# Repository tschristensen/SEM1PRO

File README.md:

# SEM1PRO
Embedded Systems and Power Electronics - Semester Project
Thomas S. Christensen
Mikkel S. Jaedicke - mijae12@student.sdu.dk
Kyriakos Dovelos
Erlingur Ívar Jóhannsson
Martin Brøchner Andersen - marti11@student.sdu.dk

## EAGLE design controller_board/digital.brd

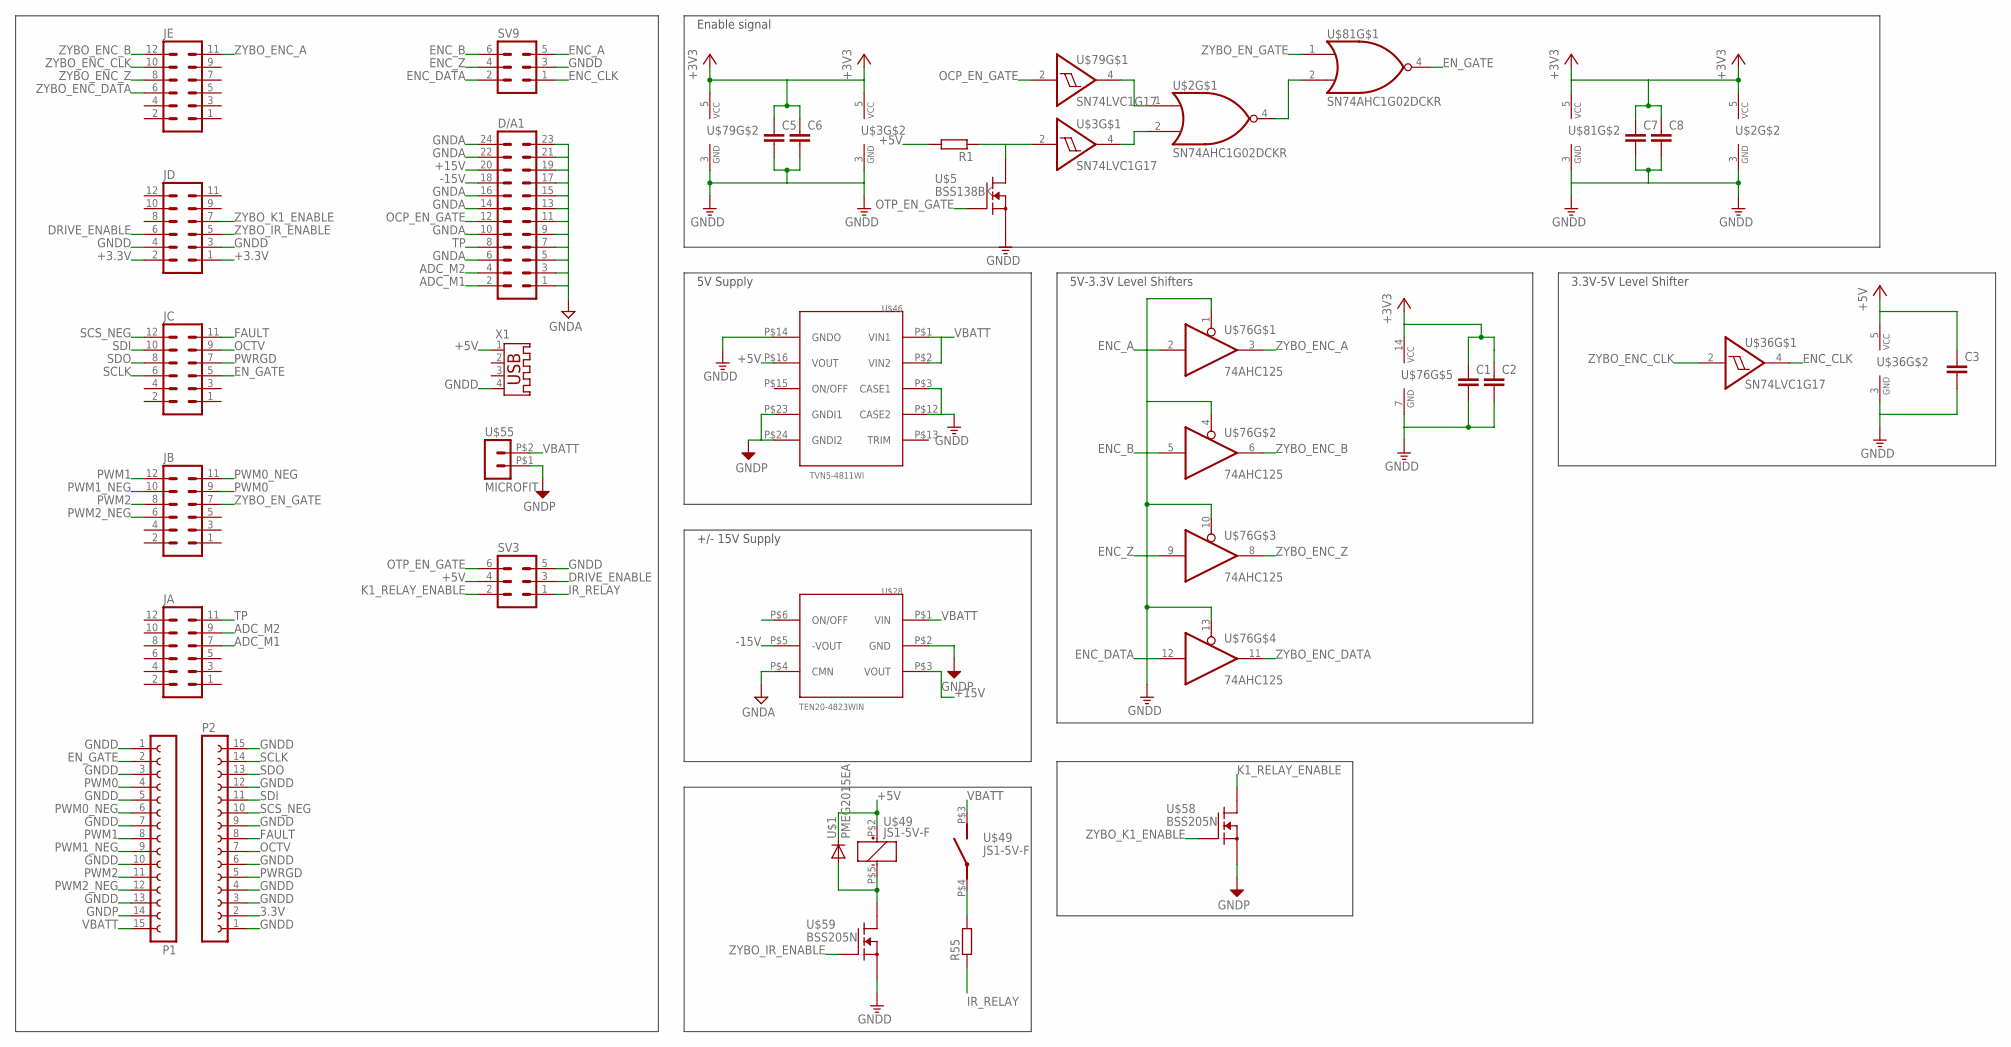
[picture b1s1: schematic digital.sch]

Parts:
C1, C2, C3, C5, C6, C7, C8: CC1206; C1206
D/A1: MA12-2
JA: MA06-2
JB: MA06-2
JC: MA06-2
JD: MA06-2
JE: MA06-2
P1, P2: FE15-1; FE15
R1, R55: RR1206; R1206
SV3, SV9: MA03-2
U$1: PMEG2015EA; SOD323_ST
U$2, U$81: SN74AHC1G02DCKR; SOT23-5
U$3, U$36, U$79: SN74LVC1G17; SOT23-5L
U$5: BSS138BK; SOT23
U$28: TEN20-4823WIN; TEN20-4823
U$46: TVN5-4811WI; DIP24
U$49: JS1-5V-F
U$55: MICROFIT; MICROFIT-3.0
U$58, U$59: BSS205N; SOT23
U$76: 74AHC125; SO14
X1: USB-A003

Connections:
3.3V: P2.2
+3.3V: JD.1, JD.2
+3V3: C1.1, C2.1, C5.1, C6.1, C7.1, C8.1, U$2.5 (VCC), U$3.5 (VCC), U$76.14 (VCC), U$79.5 (VCC), U$81.5 (VCC)
+5V: C3.1, R1.2, SV3.4, U$1.C, U$36.5 (VCC), U$46.P$16 (VOUT), U$49.P$2 (+), X1.1
+15V: D/A1.20, U$28.P$3 (VOUT)
-15V: D/A1.18, U$28.P$5 (-VOUT)
ADC_M1: D/A1.2, JA.7
ADC_M2: D/A1.4, JA.9
DRIVE_ENABLE: JD.6, SV3.3
ENC_A: SV9.5, U$76.2 (I)
ENC_B: SV9.6, U$76.5 (I)
ENC_CLK: SV9.1, U$36.4 (O)
ENC_DATA: SV9.2, U$76.12 (I)
ENC_Z: SV9.4, U$76.9 (I)
EN_GATE: JC.5, P1.2, U$81.4 (O)
FAULT: JC.11, P2.8
GNDA: D/A1.1, D/A1.3, D/A1.5, D/A1.6, D/A1.7, D/A1.9, D/A1.10, D/A1.11, D/A1.13, D/A1.14, D/A1.15, D/A1.16, D/A1.22, D/A1.23, D/A1.24, U$28.P$4 (CMN)
GNDD: C1.2, C2.2, C3.2, C5.2, C6.2, C7.2, C8.2, JD.3, JD.4, P1.1, P1.3, P1.5, P1.7, P1.10, P1.13, P2.1, P2.3, P2.4, P2.6, P2.9, P2.12, P2.15, SV3.5, SV9.3, U$2.3 (GND), U$3.3 (GND), U$5.2 (S), U$36.3 (GND), U$46.P$3 (CASE1), U$46.P$12 (CASE2), U$46.P$14 (GNDO), U$59.2 (S), U$76.1 (OE), U$76.4 (OE), U$76.7 (GND), U$76.10 (OE), U$76.13 (OE), U$79.3 (GND), U$81.3 (GND), X1.4
GNDP: P1.14, U$28.P$2 (GND), U$46.P$23 (GNDI1), U$46.P$24 (GNDI2), U$55.P$1 (2), U$58.2 (S)
IR_RELAY: R55.1, SV3.1
K1_RELAY_ENABLE: SV3.2, U$58.3 (D)
unnamed: R1.1, U$3.2 (I), U$5.3 (D)
unnamed: U$2.4 (O), U$81.2 (I1)
unnamed: R55.2, U$49.P$4
unnamed: U$1.A, U$49.P$5 (-), U$59.3 (D)
OCP_EN_GATE: D/A1.12, U$79.2 (I)
OCTV: JC.9, P2.7
OTP_EN_GATE: SV3.6, U$5.1 (G)
PWM0: JB.9, P1.4
PWM0_NEG: JB.11, P1.6
PWM1: JB.12, P1.8
PWM1_NEG: JB.10, P1.9
PWM2: JB.8, P1.11
PWM2_NEG: JB.6, P1.12
PWRGD: JC.7, P2.5
SCLK: JC.6, P2.14
SCS_NEG: JC.12, P2.10
SDI: JC.10, P2.11
SDO: JC.8, P2.13
TP: D/A1.8, JA.11
VBATT: P1.15, U$28.P$1 (VIN), U$46.P$1 (VIN1), U$46.P$2 (VIN2), U$49.P$3 (S), U$55.P$2 (3)
ZYBO_ENC_A: JE.11, U$76.3 (O)
ZYBO_ENC_B: JE.12, U$76.6 (O)
ZYBO_ENC_CLK: JE.10, U$36.2 (I)
ZYBO_ENC_DATA: JE.6, U$76.11 (O)
ZYBO_ENC_Z: JE.8, U$76.8 (O)
ZYBO_EN_GATE: JB.7, U$81.1 (I0)
ZYBO_IR_ENABLE: JD.5, U$59.1 (G)
ZYBO_K1_ENABLE: JD.7, U$58.1 (G)
ZYBO_OCP_EN_GATE: JB.5, U$2.1 (I0), U$79.4 (O)
ZYBO_OTP_EN_GATE: JD.8, U$2.2 (I1), U$3.4 (O)

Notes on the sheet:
Enable signal
5V-3.3V Level Shifters
3.3V-5V Level Shifter
+/- 15V Supply
5V Supply

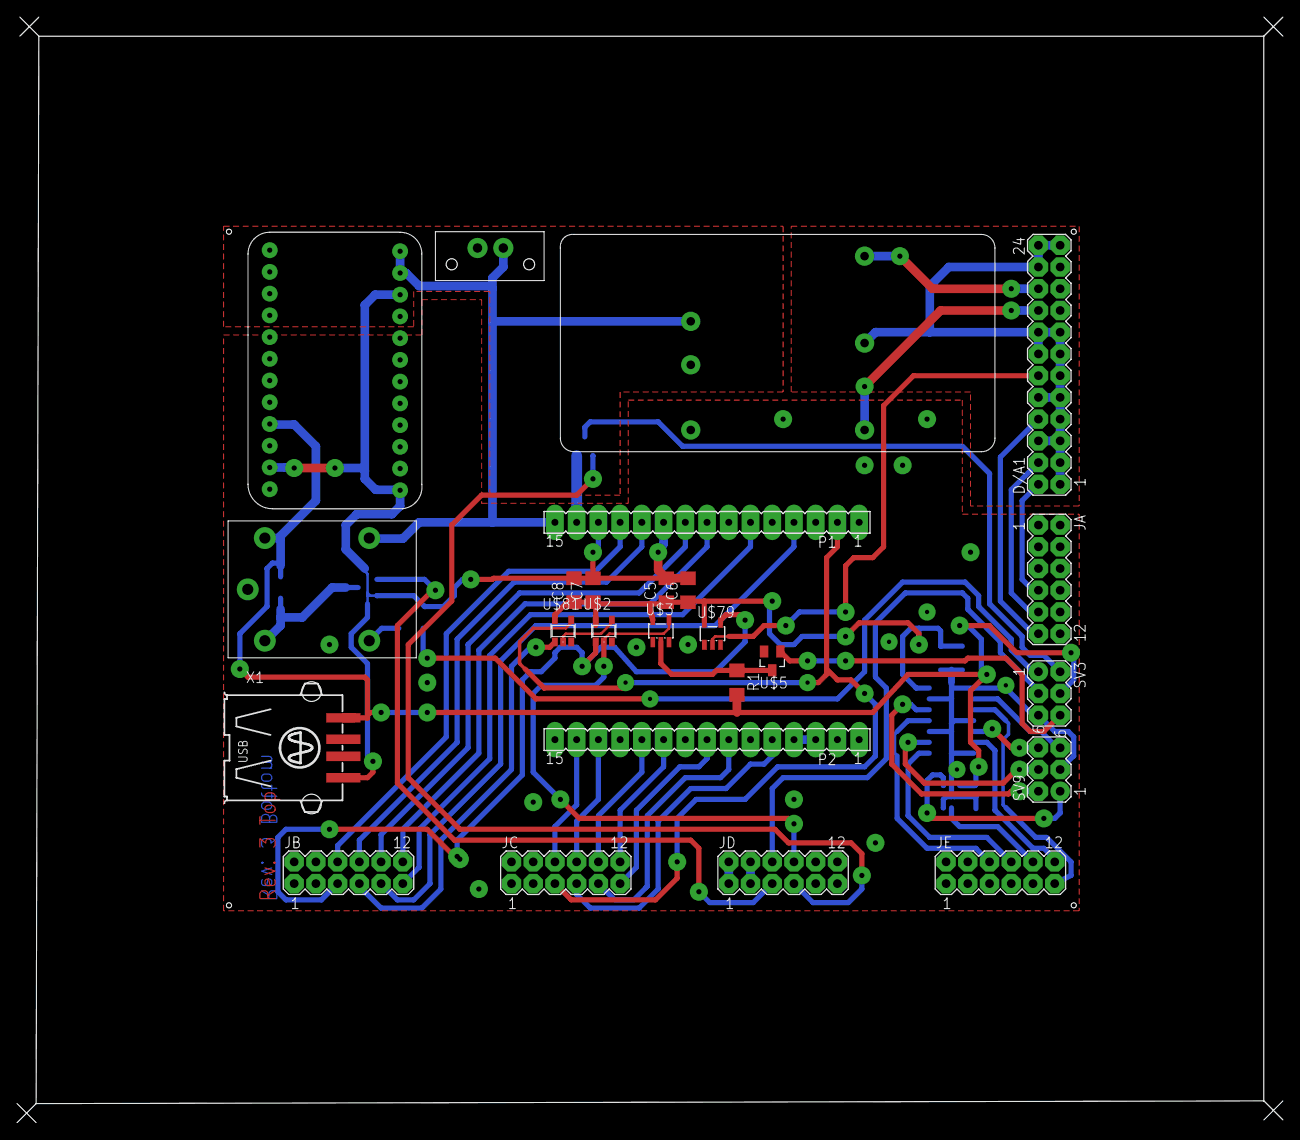
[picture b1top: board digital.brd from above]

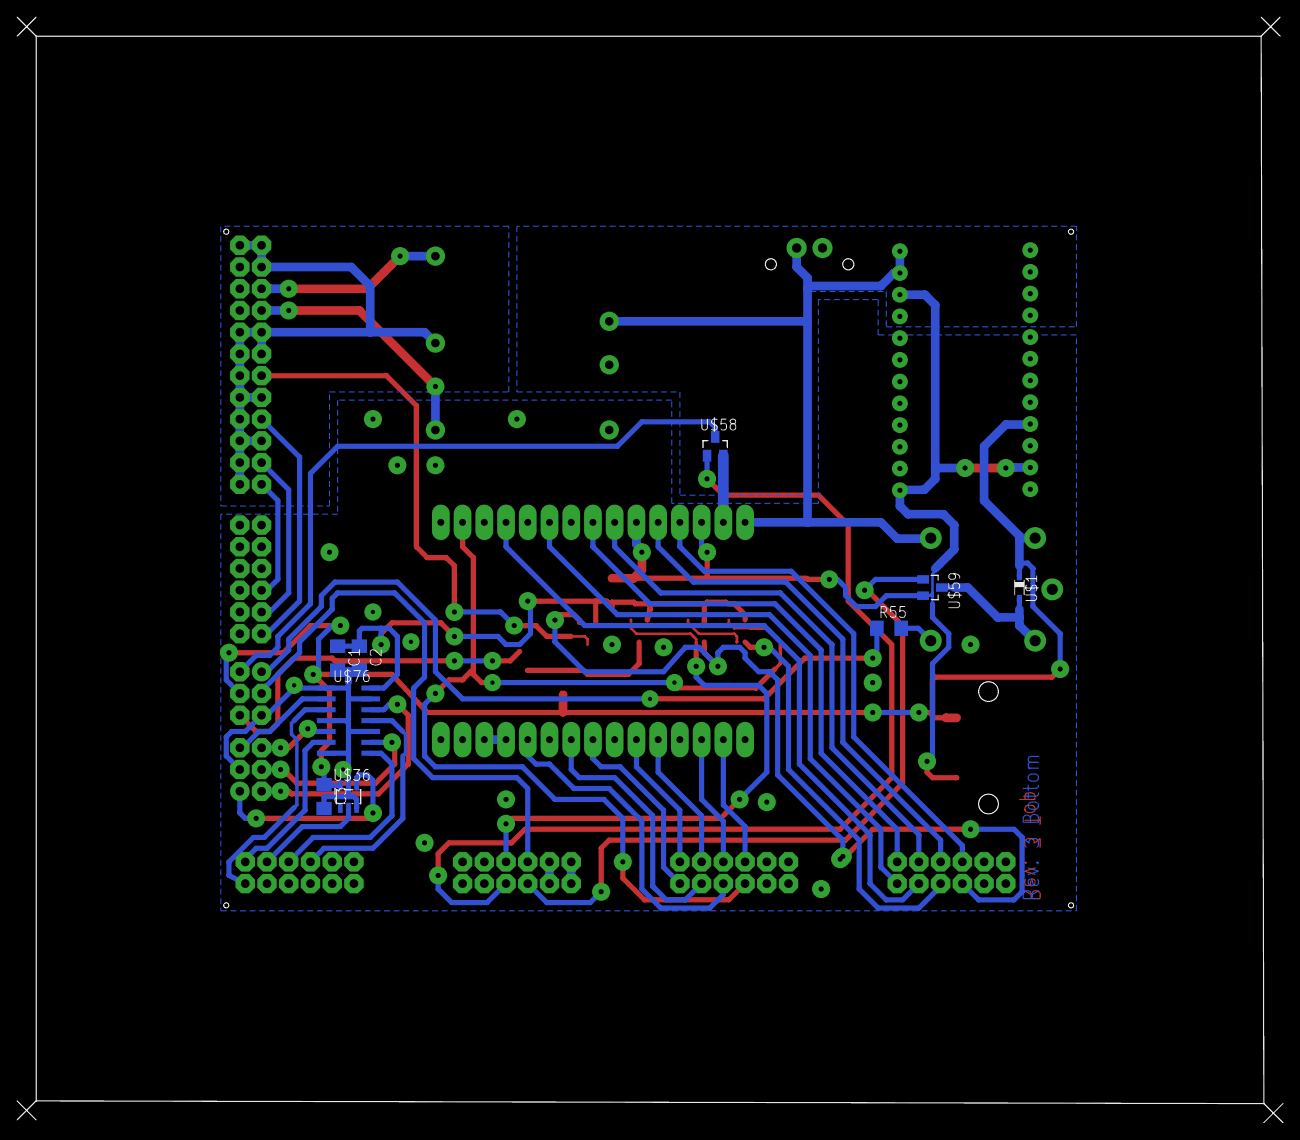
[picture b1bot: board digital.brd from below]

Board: 2 copper layers, 148.0 x 129.2 mm, 34 parts (9 on the bottom side), 50 nets.

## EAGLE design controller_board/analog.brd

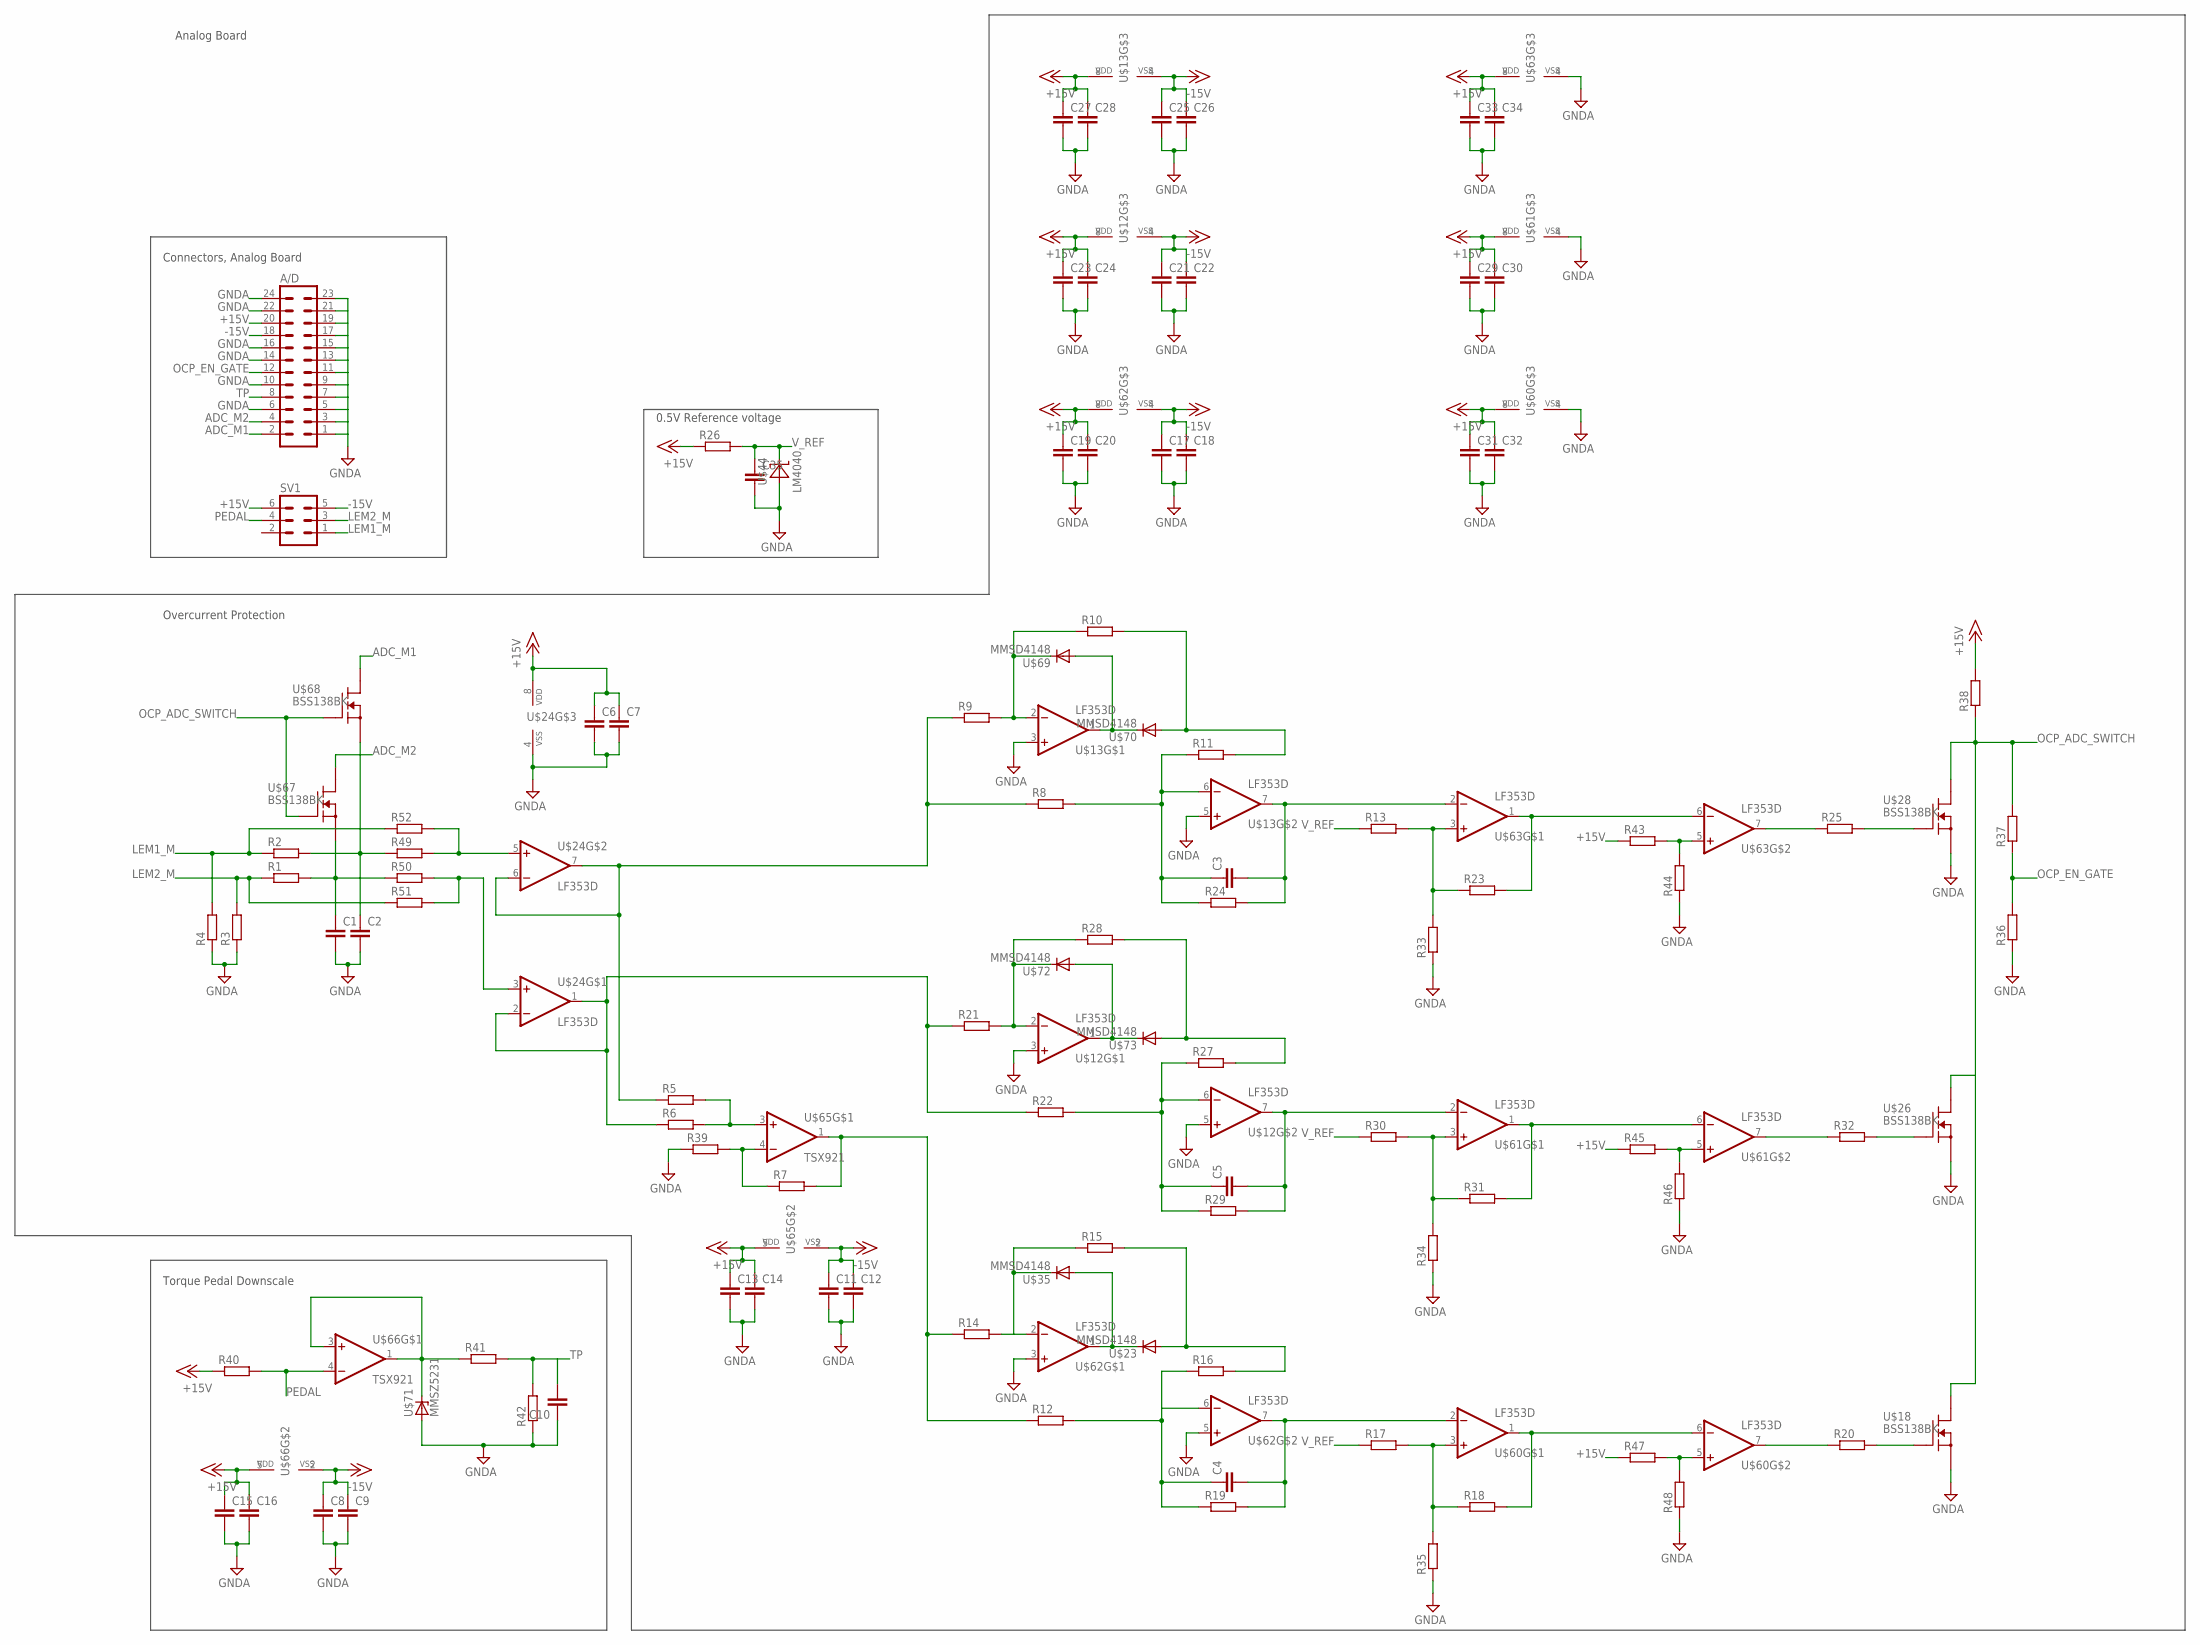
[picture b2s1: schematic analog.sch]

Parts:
A/D: MA12-2
C1, C2, C6, C7, C8, C9, C11, C12, C13, C14, C15, C16, C17, C18, C19, C20, C21, C22, C23, C24, C25, C26, C27, C28, C29, C30, C31, C32, C33, C34, C35: CC1206; C1206
C3, C4, C5, C10: C-EUC0805; C0805
R1, R2, R3, R4, R5, R6, R7, R8, R9, R10, R11, R12, R13, R14, R15, R16, R17, R18, R19, R20, R21, R22, R23, R24, R25, R26, R27, R28, R29, R30, R31, R32, R33, R34, R35, R36, R37, R38, R39, R40, R41, R42, R43, R44, R45, R46, R47, R48, R49, R50, R51, R52: R-EU_M0805; M0805
SV1: MA03-2
U$12, U$13, U$24, U$60, U$61, U$62, U$63: LF353D; SO08
U$18, U$26, U$28, U$67, U$68: BSS138BK; SOT23
U$23, U$35, U$69, U$70, U$72, U$73: MMSD4148; SOD123
U$44: LM4040; SOT23
U$65, U$66: TSX921; SOT23-5
U$71: MMSZ5231; SOD123

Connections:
+15V: A/D.20, C6.1, C7.1, C13.1, C14.1, C15.1, C16.1, C19.1, C20.1, C23.1, C24.1, C27.1, C28.1, C29.1, C30.1, C31.1, C32.1, C33.1, C34.1, R26.1, R38.2, R40.1, R43.1, R45.1, R47.1, SV1.6, U$12.8 (VDD), U$13.8 (VDD), U$24.8 (VDD), U$60.8 (VDD), U$61.8 (VDD), U$62.8 (VDD), U$63.8 (VDD), U$65.5 (VDD), U$66.5 (VDD)
-15V: A/D.18, C8.1, C9.1, C11.1, C12.1, C17.1, C18.1, C21.1, C22.1, C25.1, C26.1, SV1.5, U$12.4 (VSS), U$13.4 (VSS), U$62.4 (VSS), U$65.2 (VSS), U$66.2 (VSS)
ADC_M1: A/D.2, U$68.3 (D)
ADC_M2: A/D.4, U$67.3 (D)
GNDA: A/D.1, A/D.3, A/D.5, A/D.6, A/D.7, A/D.9, A/D.10, A/D.11, A/D.13, A/D.14, A/D.15, A/D.16, A/D.22, A/D.23, A/D.24, C1.2, C2.2, C6.2, C7.2, C8.2, C9.2, C10.1, C11.2, C12.2, C13.2, C14.2, C15.2, C16.2, C17.2, C18.2, C19.2, C20.2, C21.2, C22.2, C23.2, C24.2, C25.2, C26.2, C27.2, C28.2, C29.2, C30.2, C31.2, C32.2, C33.2, C34.2, C35.2, R3.1, R4.1, R33.1, R34.1, R35.1, R36.1, R39.1, R42.1, R44.1, R46.1, R48.1, U$12.3 (+IN), U$12.5 (+IN), U$13.3 (+IN), U$13.5 (+IN), U$18.2 (S), U$24.4 (VSS), U$26.2 (S), U$28.2 (S), U$44.1 (A), U$60.4 (VSS), U$61.4 (VSS), U$62.3 (+IN), U$62.5 (+IN), U$63.4 (VSS), U$71.A
LEM1_M: R2.1, R4.2, R52.1, SV1.1
LEM2_M: R1.1, R3.2, R51.1, SV1.3
unnamed: R50.2, R51.2, U$24.3 (+IN)
unnamed: R5.1, R8.1, R9.1, U$24.6 (-IN), U$24.7 (OUT)
unnamed: R9.2, R10.1, U$13.2 (-IN), U$69.C
unnamed: C2.1, R2.2, R49.1, U$68.2 (S)
unnamed: R13.2, R23.1, R33.2, U$63.3 (+IN)
unnamed: R5.2, R6.2, U$65.3 (+IN)
unnamed: R7.2, R12.1, R14.1, U$65.1 (OUT)
unnamed: C3.1, R8.2, R11.1, R24.1, U$13.6 (-IN)
unnamed: R10.2, R11.2, U$70.A
unnamed: C3.2, R24.2, U$13.7 (OUT), U$63.2 (-IN)
unnamed: U$13.1 (OUT), U$69.A, U$70.C
unnamed: R6.1, R21.1, R22.1, U$24.1 (OUT), U$24.2 (-IN)
unnamed: R14.2, R15.1, U$35.C, U$62.2 (-IN)
unnamed: C4.1, R12.2, R16.1, R19.1, U$62.6 (-IN)
unnamed: U$23.C, U$35.A, U$62.1 (OUT)
unnamed: R15.2, R16.2, U$23.A
unnamed: C4.2, R19.2, U$60.2 (-IN), U$62.7 (OUT)
unnamed: R23.2, U$63.1 (OUT), U$63.6 (-IN)
unnamed: R17.2, R18.1, R35.2, U$60.3 (+IN)
unnamed: R18.2, U$60.1 (OUT), U$60.6 (-IN)
unnamed: R32.1, U$61.7 (OUT)
unnamed: R7.1, R39.2, U$65.4 (-IN)
unnamed: R21.2, R28.1, U$12.2 (-IN), U$72.C
unnamed: C5.1, R22.2, R27.1, R29.1, U$12.6 (-IN)
unnamed: U$12.1 (OUT), U$72.A, U$73.C
unnamed: R27.2, R28.2, U$73.A
unnamed: C5.2, R29.2, U$12.7 (OUT), U$61.2 (-IN)
unnamed: R30.2, R31.1, R34.2, U$61.3 (+IN)
unnamed: R31.2, U$61.1 (OUT), U$61.6 (-IN)
unnamed: R45.2, R46.2, U$61.5 (+IN)
unnamed: R25.1, U$63.7 (OUT)
unnamed: R25.2, U$28.1 (G)
unnamed: R32.2, U$26.1 (G)
unnamed: R20.2, U$18.1 (G)
unnamed: R41.1, U$66.1 (OUT), U$66.3 (+IN), U$71.C
unnamed: R43.2, R44.2, U$63.5 (+IN)
unnamed: R47.2, R48.2, U$60.5 (+IN)
unnamed: R20.1, U$60.7 (OUT)
unnamed: R49.2, R52.2, U$24.5 (+IN)
unnamed: C1.1, R1.2, R50.1, U$67.2 (S)
OCP_ADC_SWITCH: R37.2, R38.1, U$18.3 (D), U$26.3 (D), U$28.3 (D), U$67.1 (G), U$68.1 (G)
OCP_EN_GATE: A/D.12, R36.2, R37.1
PEDAL: R40.2, SV1.4, U$66.4 (-IN)
TP: A/D.8, C10.2, R41.2, R42.2
V_REF: C35.1, R13.1, R17.1, R26.2, R30.1, U$44.2 (C)

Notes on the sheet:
Torque Pedal Downscale
Overcurrent Protection
0.5V Reference voltage
Analog Board
Connectors, Analog Board

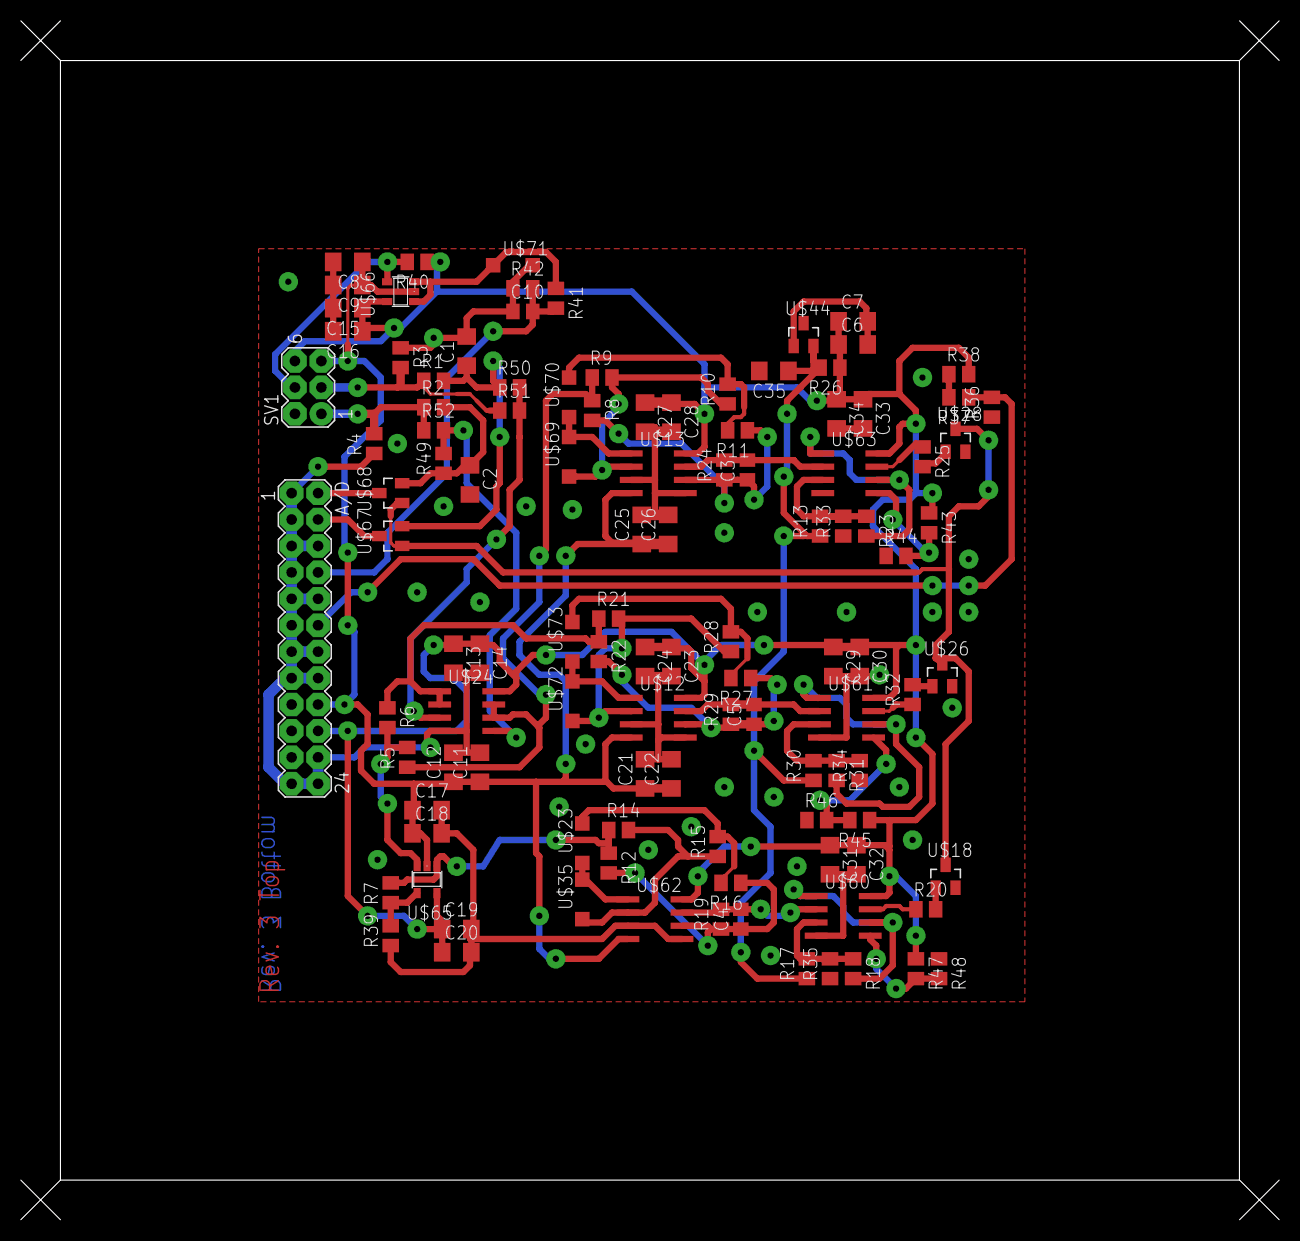
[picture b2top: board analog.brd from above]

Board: 2 copper layers, 121.0 x 115.3 mm, 111 parts (0 on the bottom side), 52 nets.

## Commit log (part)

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2016-03-09 edit my name
2016-03-09 Message
2016-03-09 Added my name and email
2016-03-09 Conflict Resolved!
2016-03-09 lkljlkj
2016-03-09 added a name
2016-03-09 Test
2016-03-09 useless
2016-03-15 Added initial report structure and .gitignore
2016-03-16 Added my date of birth
2016-03-16 added a name to the readme.md file
2016-03-16 Added my name, and wrote the RIGHT email.
2016-03-16 Uploaded my four suggestions for power transistors
2016-03-17 Added name to titlepage and configuration line for my system
2016-03-17 inserted birthday
2016-04-01 added schematics
2016-04-01 added schematic pdf
2016-04-07 added Note for logic level converters
2016-04-10 added some pics
2016-04-10 Added datasheets for controller and buckconverter + initial draft of logic level converters and Torque pedal scaledown
2016-04-10 more datasheets
2016-04-13 Added figures for controller board section
2016-04-14 set up the report to include all the sections i think are needed.
2016-04-14 Added board schematic
2016-04-14 added pic
2016-04-14 updated board scematic
2016-04-14 Yet another schematic update!
2016-04-20 added TI application note and updates to report
2016-04-20 report changed a little. some sections added
2016-04-21 agenda
2016-04-21 meeting agenda updated.
2016-04-22 Started writing on PMACmotor
2016-04-22 Added simulation folder with lots of nice stuff to be confused about
2016-04-22 updated simulations, added KE measurements
2016-04-22 added full system diagram V1.0
2016-04-22 just some more words
2016-04-24 wrote some more on PMAC
2016-04-25 added battery to resources and started writing system discription
2016-04-25 edited bib.tex, and added datasheets (I think)
2016-04-26 added plecs model with PWM switch mode and heatsinks
2016-04-27 Added small motor project
2016-04-27 blank
2016-04-28 updatet power loss simulations
2016-04-30 Added BOM for analog board
2016-05-02 so this cannot be empty?
2016-05-03 Got tortoiseGit (for windows) working. And uploaded datasheet for our mosfets.
2016-05-04 Plecs models with and without SVN
2016-05-04 blockdiagram
2016-05-04 added blockdiagram
2016-05-04 no changes made. i just checked the diagram
2016-05-04 added small_motor3 project
2016-05-04 Added board schematics and board layouts, open with eagle
2016-05-04 fixed introduction
2016-05-04 Started writing on Simulations
2016-05-05 fixed an error
2016-05-05 Uploaded possibly faulty simulation
2016-05-05 controller changes
2016-05-05 Uploaded document about scmitt triggers
2016-05-05 Pull commit
2016-05-05 A days work on simulation.tex, and general simulations.
2016-05-05 Discretesized controller-
2016-05-06 Fixed diagram
2016-05-06 Updated simulations. Now I'll head home, and have my desktop work on them for a day or two.
2016-05-06 writing system overview
2016-05-06 writing more to system descrption.
2016-05-06 okok
2016-05-07 changed pictures. they were too big, took ages to build.
2016-05-07 more writing. system stuff
2016-05-07 Did some simulations
2016-05-08 In simulations: Quantized encoder feedback, switched to lookup tables (realistic, not sure it's any faster in simulations). Wrote more about Simulations.
2016-05-09 changed filenames. PNG -> png
2016-05-09 Uploaded rough version of board documentation
2016-05-09 Added graphics for boardlayout
2016-05-09 skod program
2016-05-09 Added meeting details from today
2016-05-09 meeting details
2016-05-09 Pedal
2016-05-09 diagrams
2016-05-09 Added PMSM state space model and paper about state space.
2016-05-09 Half days work
2016-05-10 PDF DIAGRAMS
2016-05-10 fixed something
2016-05-10 Revision of Diagrams
2016-05-10 pdf also
2016-05-10 added some mosfet stuff
2016-05-10 made small adjustmens of text and added lots of todos
2016-05-10 Model changes state space. made transfer function.
2016-05-11 added figures of motor model
2016-05-11 Added section of logic level shifters and drive enable signals!
2016-05-11 control ki kp added
2016-05-11 worked on the model.
2016-05-12 found kp and ki from transfer function + settling time formula.
2016-05-12 wrote comments to the control parameters
2016-05-12 updates to boards
2016-05-12 added some text and stuff
2016-05-12 Added a new section for the state space model and finding parameters of kp and ki. added 5 graphics and changed main file.
2016-05-12 fixed motor model figs
2016-05-12 added driver enable signal bit
2016-05-13 writing continues
2016-05-13 uploading graphics fix
2016-05-13 added some text n' stuff
2016-05-13 wrote about transfer function and deriving control values
2016-05-13 introduction.tex AND REF
2016-05-13 did nothing
2016-05-13 added graphic
2016-05-13 added missing figures
2016-05-13 fixed some errors
2016-05-14 Managed to add a crude brake and tire slip. Pretty proud of it, just have to fine tune it.
2016-05-14 Tweaked the brake
2016-05-16 added more report
2016-05-16 removed controller board section, this is replaced by boardlayout
2016-05-16 New report structure and tons of todos
2016-05-16 added extended layout section
2016-05-16 added a tiny bit
2016-05-16 no changes
2016-05-16 added a lot to system description
2016-05-16 added a bit
2016-05-16 added many more todos and the siunitx package
2016-05-16 fixed main
2016-05-16 changs to system diagram
2016-05-16 added graphics
2016-05-16 More todos,
2016-05-17 added section about small test
2016-05-17 added graph
2016-05-17 Read through PMAC
2016-05-17 added an ADC section
2016-05-17 Done reading and todoing this revision, except controller part
2016-05-17 added small section about encoders
2016-05-17 Responded to the comments, Thomas made to some of my text.
2016-05-17 Remade some diagrams for the zybo section with tikz, wrote a lot more to state space model section and added some pictures. Still need a lot of work on model section.
2016-05-17 changed the figures to tikz in zybo section
2016-05-17 Plecs
2016-05-19 Added/changed system analysis slightly
2016-05-20 writings from yesterday.
2016-05-21 Some model/control changes. + writing
2016-05-21 added Xilinx project
2016-05-21 Who knows!
2016-05-21 removed big file
2016-05-21 fixed mistake
2016-05-21 lots of changes to model stuff.
2016-05-22 Added some sunday graphs
2016-05-23 new task diagram updated
2016-05-23 nothing special
2016-05-23 corrections
2016-05-23 cccc
2016-05-23 added stuff about mosfets, not finished
2016-05-23 new pictures. more text. more correctness
2016-05-24 aaaa
2016-05-24 trying to correct and extend intro
2016-05-24 added some figs and more
2016-05-24 changes to stuff nd junk! mostly controller stuff
2016-05-25 Changes to Electronics Design
2016-05-25 added missing picture...
2016-05-25 task diagram changes
2016-05-25 small changes
2016-05-25 added Kyriakos's thing
2016-05-25 finished control
2016-05-25 More SPI and change to main.tex to make figure texts smaller
2016-05-25 more spi...
2016-05-25 sada
2016-05-25 Little bit of writing, little bit of simulations. Lots of analog board work, but that's not evident here.
2016-05-26 fixing an error
2016-05-26 added ocp data
2016-05-26 Wrote a lot about pole zero
2016-05-26 Added some text!
2016-05-26 George managed to get me thinking so I couldn't fall asleep. Turns out I'm still right
2016-05-27 Writing stuff
2016-05-27 removed Kyriakos text and added some definements for my code
2016-05-27 ocp underscore data
2016-05-27 done deal
2016-05-27 added text about controller
2016-05-27 little bit reading through motormodel.tex
2016-05-27 Writing on Simulations
2016-05-28 fixed data
2016-05-28 fixed some shit
2016-05-28 Fixed bib.tex
2016-05-28 Baaaaaaaaaaaaaaaaaah, annoying
2016-05-28 I don't remember what I did
2016-05-28 added missing graphics
2016-05-28 pulpupllpullpul
2016-05-28 added missing grpahics
2016-05-28 lalallalala
2016-05-28 added tikz
2016-05-28 added graph and text
2016-05-28 workworkworkworkwork
2016-05-28 Added half inverter section
2016-05-28 added task digram
2016-05-28 added single phase diagram
2016-05-28 adding to mosfet section
2016-05-28 more tikz
2016-05-28 added some and tried to change titlepage. Not finished. We should tallk.
2016-05-28 Fucking real madrid won. Now I'm sad!
2016-05-28 Still sad!
2016-05-28 my zection is readzy!
2016-05-28 added more stuff to mosfets and some figs
2016-05-29 changed all figures in my section. Trim is fucking me over though. will fix tomorrow
2016-05-29 sooo tired
2016-05-29 Added a main.tex file without all the sections ignored.
2016-05-29 readtrough of electronic part
2016-05-29 Todos in Mikkels section
2016-05-29 Looked through threephaseinverter.tex, and commented on what I saw. It's still too short for my taste.
2016-05-29 something git wanted
2016-05-29 A beautiful Branch!
2016-05-29 Cropped all the pictures using NITRO! great program ! :D
2016-05-29 changed some in system anal
2016-05-29 Hello World
2016-05-29 just some un commenting
2016-05-29 redone corrections
2016-05-29 fixed some erlingur notes. not done at all. reading martins now
2016-05-29 added text about time freq
2016-05-29 Added graphics and corrections to electronics
2016-05-29 little bit confusing
2016-05-29 red through simulation added comments
2016-05-29 Beginning sections read again
2016-05-29 added nice graphs
2016-05-29 added the actual graphs
2016-05-29 some todo changes
2016-05-29 Wrote something aobut caps... it's crap
2016-05-29 added a little stupid part about inverter layout
2016-05-29 Fixed signing placement, added abstract, made doublesided
2016-05-29 little bit about test
2016-05-29 added a section about temperature, fixed some figs
2016-05-29 fixed merge conflicts
2016-05-29 corrected the controller design section. added labels to all axes of figures. added a table and some third harmonics (which is shit atm). Going home now!
2016-05-29 would not build with inverter. missing graphics
2016-05-30 control file updated
2016-05-30 fixed contrl diagram
2016-05-30 removed a few todods
2016-05-30 little bit about third harmonic
2016-05-30 PrePull
2016-05-30 Sorry. Here is the placeholder
2016-05-30 pre push... it's real good
2016-05-30 Fixed all component names
2016-05-30 Added bibitems
2016-05-30 Todo nuking!
2016-05-30 small things
2016-05-30 fixed zybo diagram
2016-05-30 replaced figure
2016-05-30 Fixed todo's in simulation.tex and added some new ones just for the hell of it
2016-05-30 added wiringdiagram
2016-05-30 added again the wiringdiagram
2016-05-30 lots of corrections to control
2016-05-30 Commit, commit
2016-05-30 pre pull
2016-05-30 old main
2016-05-30 some comment conflicts in main
2016-05-30 replaced rms to RMS in three phase section. fixed some citations and more
2016-05-30 added colors to the tables that would allow it
2016-05-30 added some stuff about temperature
2016-05-30 Changes to captions
2016-05-30 Fixed todosies
2016-05-30 somethign
2016-05-30 bertha added
2016-05-30 pwetty pitures
2016-05-30 bertha 2 og 3 added
2016-05-31 comments in main
2016-05-31 added bertha pics
2016-05-31 replacing wiringdiagram
2016-05-31 little bit in main?
2016-05-31 fixed placehodler
2016-05-31 main is including all sections right?
2016-05-31 rettede mosfets til MOSFETs
2016-05-31 fixed clark park to Clarke Park
2016-05-31 added 1 line of motivation to the abstract
2016-05-31 added section about ho-kart
2016-05-31 fixed chapter to sections and three-phase to three phase
2016-05-31 fixed dots in captions, and go-kart
2016-05-31 fixed more three phase
2016-05-31 more three phase
2016-05-31 fixed back-EMF
2016-05-31 fixed torque pedal
2016-05-31 fixed Simulink
2016-05-31 fixed heat sink, RMS, rpm
2016-05-31 fixed phi to theta
2016-05-31 fixed some unita
2016-05-31 added line about github
2016-05-31 fixed mathr
2016-05-31 control for git upload
2016-05-31 fixed caps in section names
2016-05-31 fixed some equation refs
2016-05-31 removed red color on links
2016-05-31 removed table of table
2016-05-31 removed todo about slave select delay - fixed
2016-05-31 added some words about capacitors
2016-05-31 fixed error
2016-05-31 no more digital todosgit pushgit push! Bring some champagne.. and some rundstykker
2016-05-31 fixed kts etc
2016-05-31 added a clever figurtekst
2016-05-31 made the controller task diagram nicer
2016-05-31 conclusion
2016-05-31 placed a H the right place
2016-05-31 little bit in the introduction
2016-05-31 layout commit
2016-10-08 Some simulation work for SEM2PRO
